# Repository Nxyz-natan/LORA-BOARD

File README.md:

finished pcb of the lora board this was from the starter project at hackclub 
here in 3d

and my schematics
# LORA-BOARD
LORA BOARD

dont mind the namesof the kicad files they are the lora board

| Name | Purpose | Quantity | Total Cost (USD) | Distributor |
|------|---------|----------|-----------------|-------------|
| ESP32-S3-WROOM-1-N8 | MCU | 1 | $4.77 | LCSC |
| SX1262IMLTRT | LoRa Transceiver | 1 | $3.23 | LCSC |
| U.FL Connector | RF Connector | 1 | $0.55 | LCSC |
| Resistor 10k 0402 | Resistor | 2 | $0.08 | LCSC |
| Inductor 1.8nH 0402 | RF Matching | 1 | $0.95 | LCSC |
| Inductor 15uH 0603 | Inductor | 1 | $0.54 | LCSC |
| Cap 3.9pF 0402 NP0 | RF Matching | 1 | $0.25 | LCSC |

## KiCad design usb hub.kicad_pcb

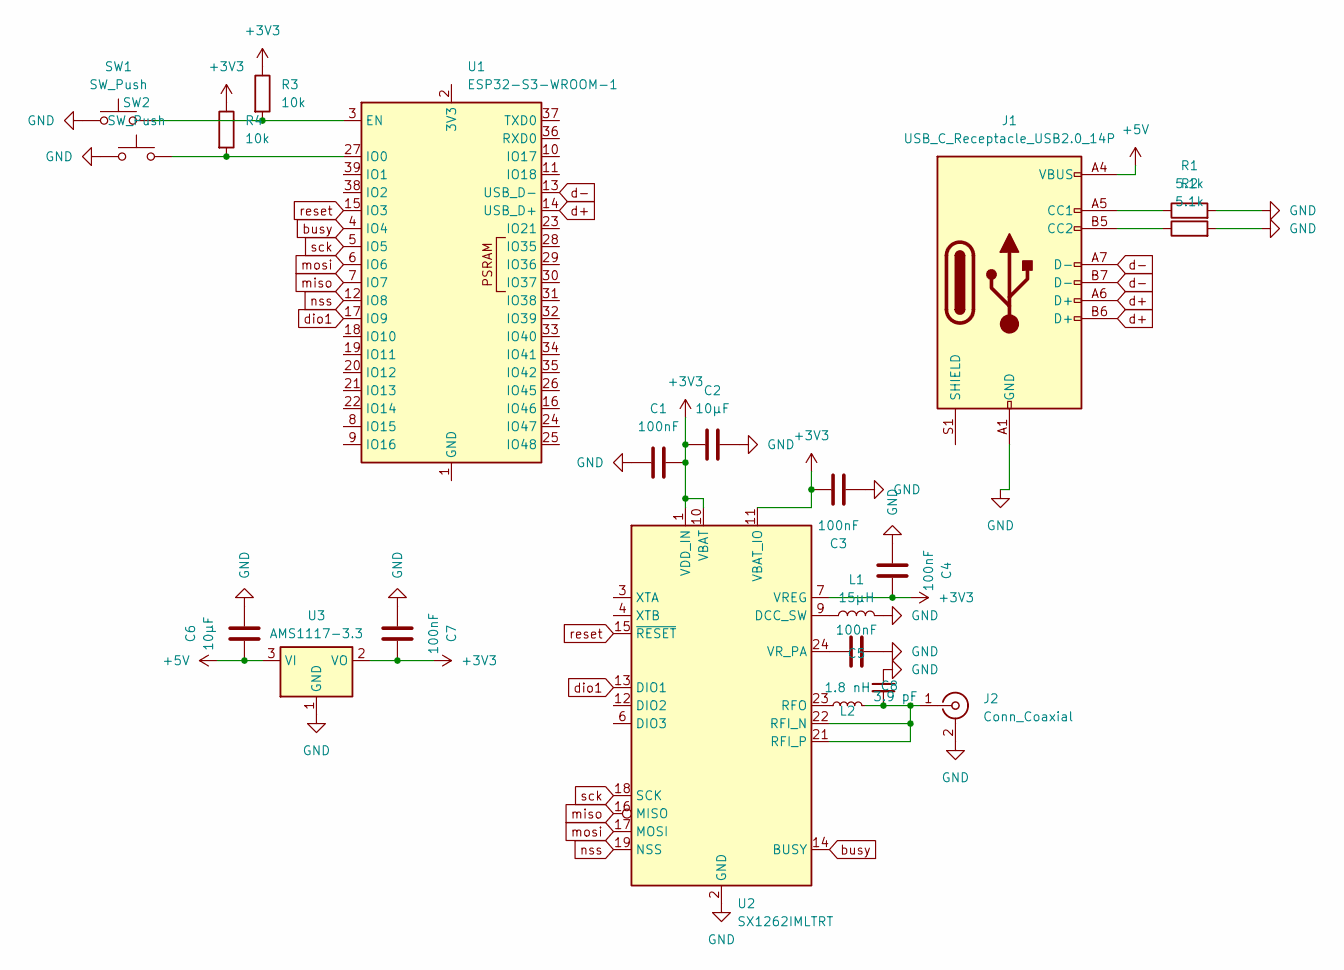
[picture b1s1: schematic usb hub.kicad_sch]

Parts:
C1, C3, C4, C5, C7: 100nF; C_0402_1005Metric
C2, C6: 10µF; C_0402_1005Metric
C8: 3.9 pF; C_0402_1005Metric
J1: USB_C_Receptacle_USB2.0_14P; USB_C_Receptacle_HRO_TYPE-C-31-M-12
J2: Conn_Coaxial; U.FL_Hirose_U.FL-R-SMT-1_Vertical
L1: 15µH; L_0603_1608Metric
L2: 1.8 nH; L_0402_1005Metric
R1, R2: 5.1k; R_0402_1005Metric
R3, R4: 10k; R_0402_1005Metric
SW1, SW2: SW_Push; SW_Push_1TS009xxxx-xxxx-xxxx_6x6x5mm
U1: ESP32-S3-WROOM-1
U2: SX1262IMLTRT; QFN-24-1EP_4x4mm_P0.5mm_EP2.6x2.6mm
U3: AMS1117-3.3; SOT-223-3_TabPin2

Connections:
+3V3: C1.2, C2.1, C3.2, C4.2, C7.2, R3.1, R4.1, U2.1 (VDD_IN), U2.7 (VREG), U2.10 (VBAT), U2.11 (VBAT_IO), U3.2 (VO)
+5V: C6.1, J1.A4 (VBUS), J1.A9 (VBUS), J1.B4 (VBUS), J1.B9 (VBUS), U3.3 (VI)
GND: C1.1, C2.2, C3.1, C4.1, C5.1, C6.2, C7.1, C8.1, J1.A1 (GND), J1.A12 (GND), J1.B1 (GND), J1.B12 (GND), J2.2 (Ext), L1.2, R1.2, R2.2, SW1.1, SW2.1, U2.2 (GND), U2.5 (GND), U2.8 (GND), U2.20 (GND), U2.25 (GND), U3.1 (GND)
unnamed: J1.A5 (CC1), R1.1
unnamed: J1.B5 (CC2), R2.1
unnamed: C8.2, J2.1 (In), L2.2, U2.21 (RFI_P), U2.22 (RFI_N)
unnamed: R3.2, SW1.2, U1.3 (EN)
unnamed: U1.1 (GND), U1.40 (GND), U1.41 (GND)
unnamed: R4.2, SW2.2, U1.27 (IO0)
unnamed: L1.1, U2.9 (DCC_SW)
unnamed: L2.1, U2.23 (RFO)
unnamed: C5.2, U2.24 (VR_PA)
busy: U1.4 (IO4), U2.14 (BUSY)
d+: J1.A6 (D+), J1.B6 (D+), U1.14 (USB_D+)
d-: J1.A7 (D-), J1.B7 (D-), U1.13 (USB_D-)
dio1: U1.17 (IO9), U2.13 (DIO1)
miso: U1.7 (IO7), U2.16 (MISO)
mosi: U1.6 (IO6), U2.17 (MOSI)
nss: U1.12 (IO8), U2.19 (NSS)
reset: U1.15 (IO3), U2.15 (~RESET)
sck: U1.5 (IO5), U2.18 (SCK)

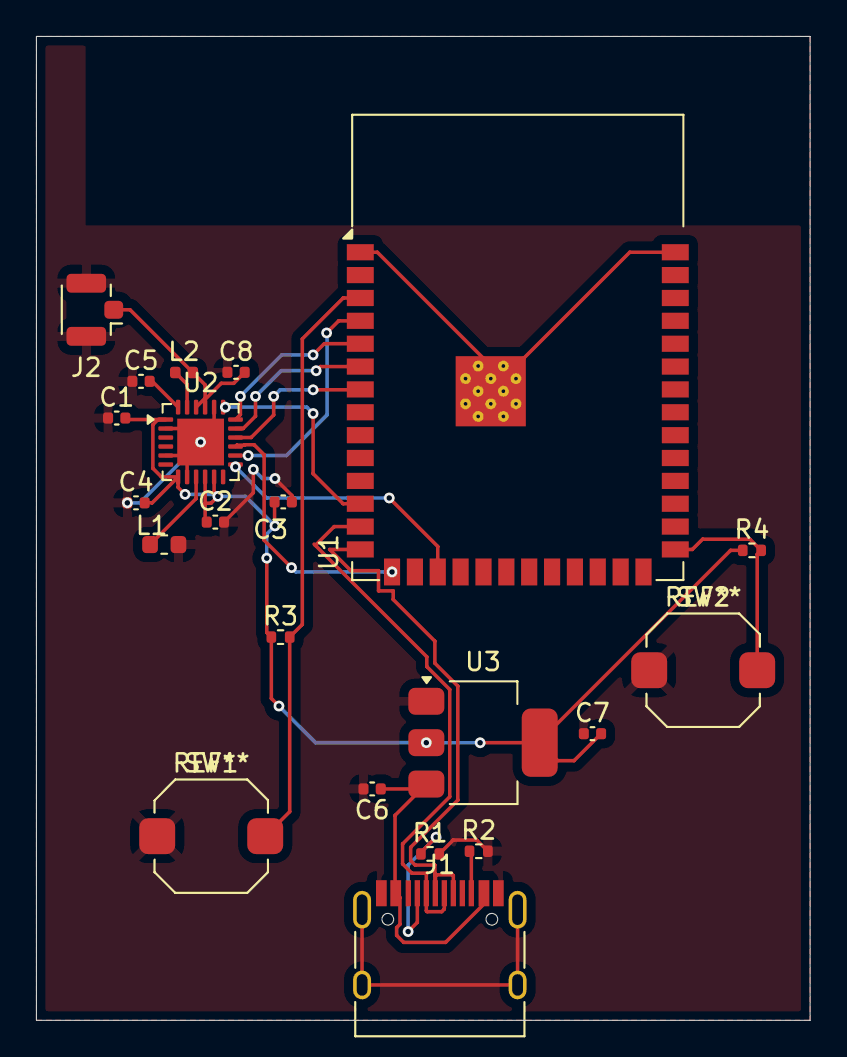
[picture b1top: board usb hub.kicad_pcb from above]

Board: 2 copper layers, 43.0 x 54.7 mm, 21 parts (0 on the bottom side), 21 nets.
